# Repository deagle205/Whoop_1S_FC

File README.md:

# Phil: 1S whoop flight controller (KiCad 10)

Three stacked 19x19 / 16x16 boards on a 12.8 mm M1.4 screw square:

- `Whoop_1S_FC.*`: flight controller (STM32G473 WLCSP-81, ICM-42688-P, SPL06, ELRS SX1281 + ESP8285, TPS63802)
- `Phil_ESC/`: 4-in-1 Bluejay ESC (4x EFM8BB51, 12x SiA517DJ)
- `Phil_VTX/`: 5.8 GHz VTX (RTC6705 + SE5004L), AT7456E OSD, blackbox flash, 5 V boost

Shared libraries: `WhoopFC.kicad_sym`, `WhoopFC.pretty/`, `WhoopFC.3dshapes/`.
Note: 3D model paths in the footprints are absolute (C:/Users/Survi/...), so other machines won't show them without editing.

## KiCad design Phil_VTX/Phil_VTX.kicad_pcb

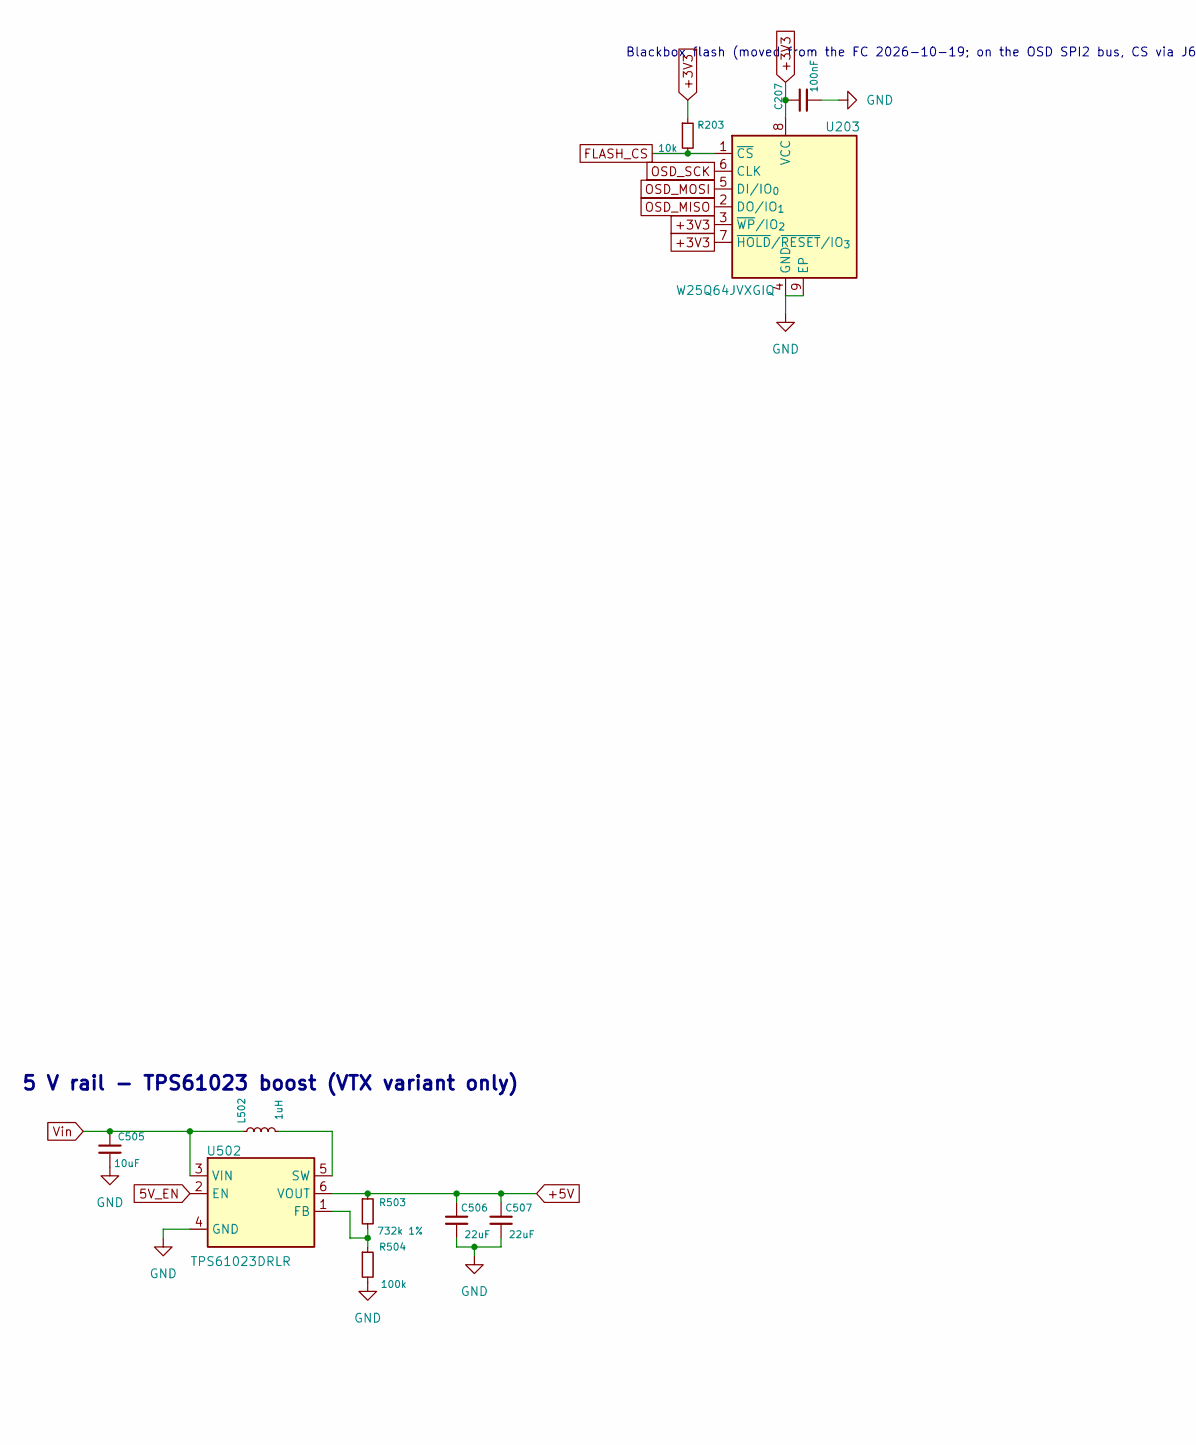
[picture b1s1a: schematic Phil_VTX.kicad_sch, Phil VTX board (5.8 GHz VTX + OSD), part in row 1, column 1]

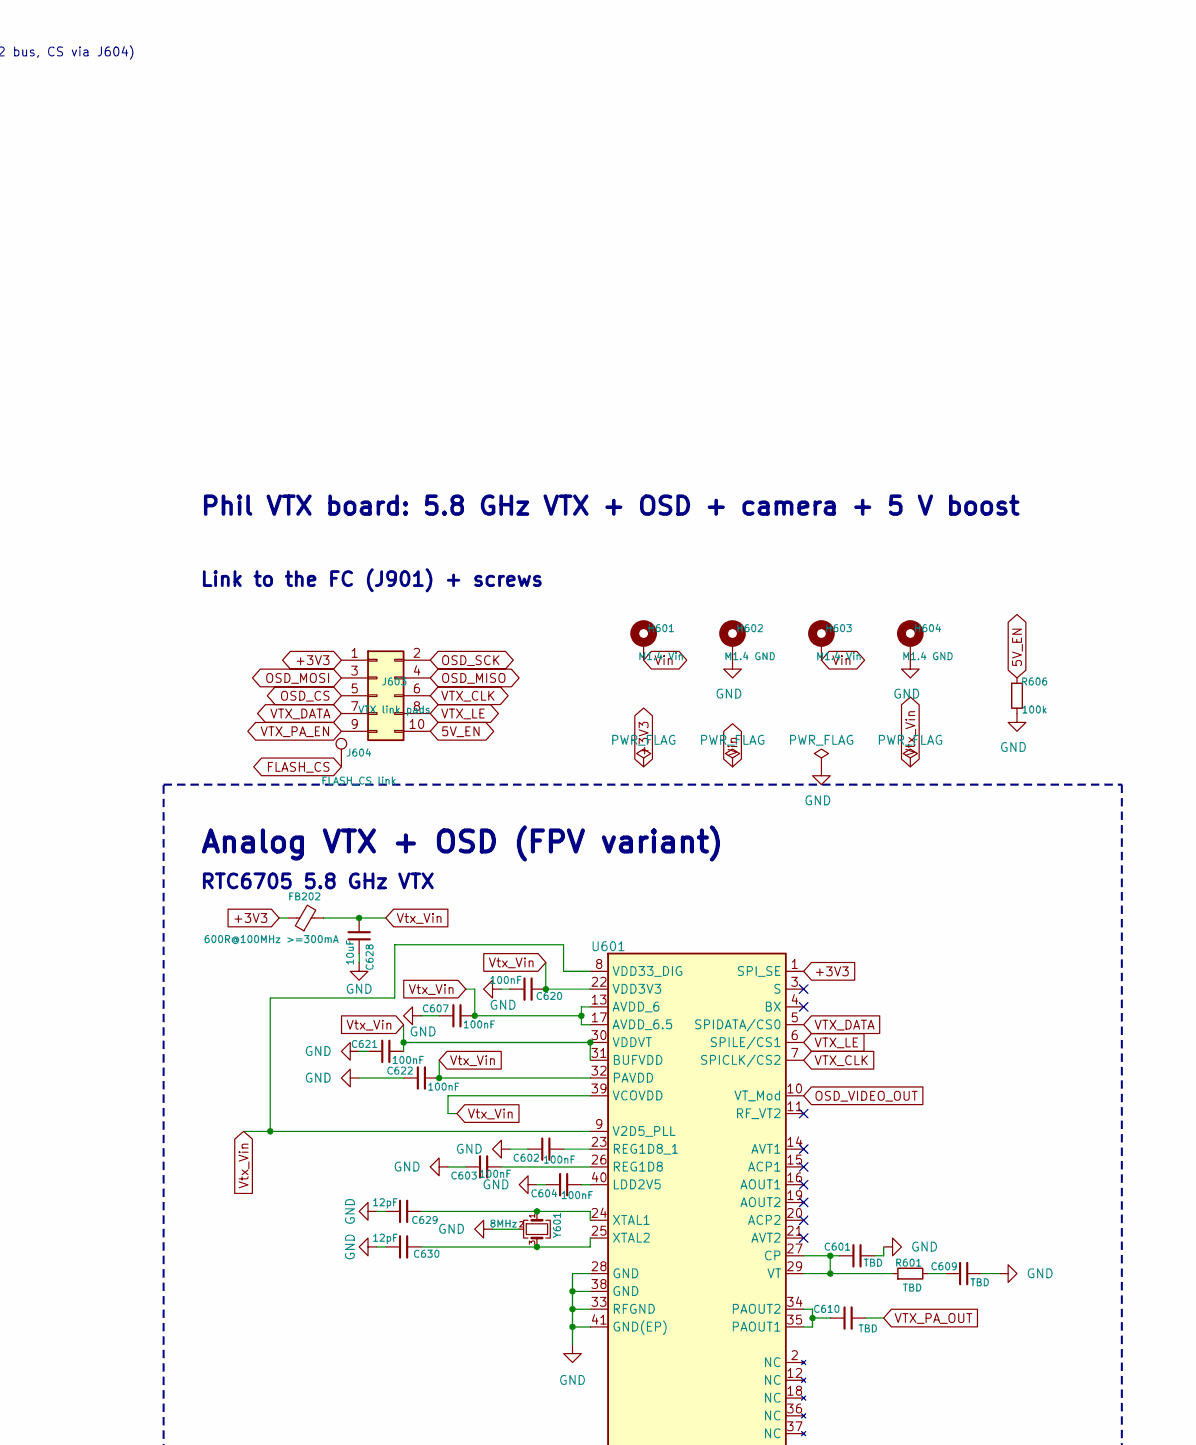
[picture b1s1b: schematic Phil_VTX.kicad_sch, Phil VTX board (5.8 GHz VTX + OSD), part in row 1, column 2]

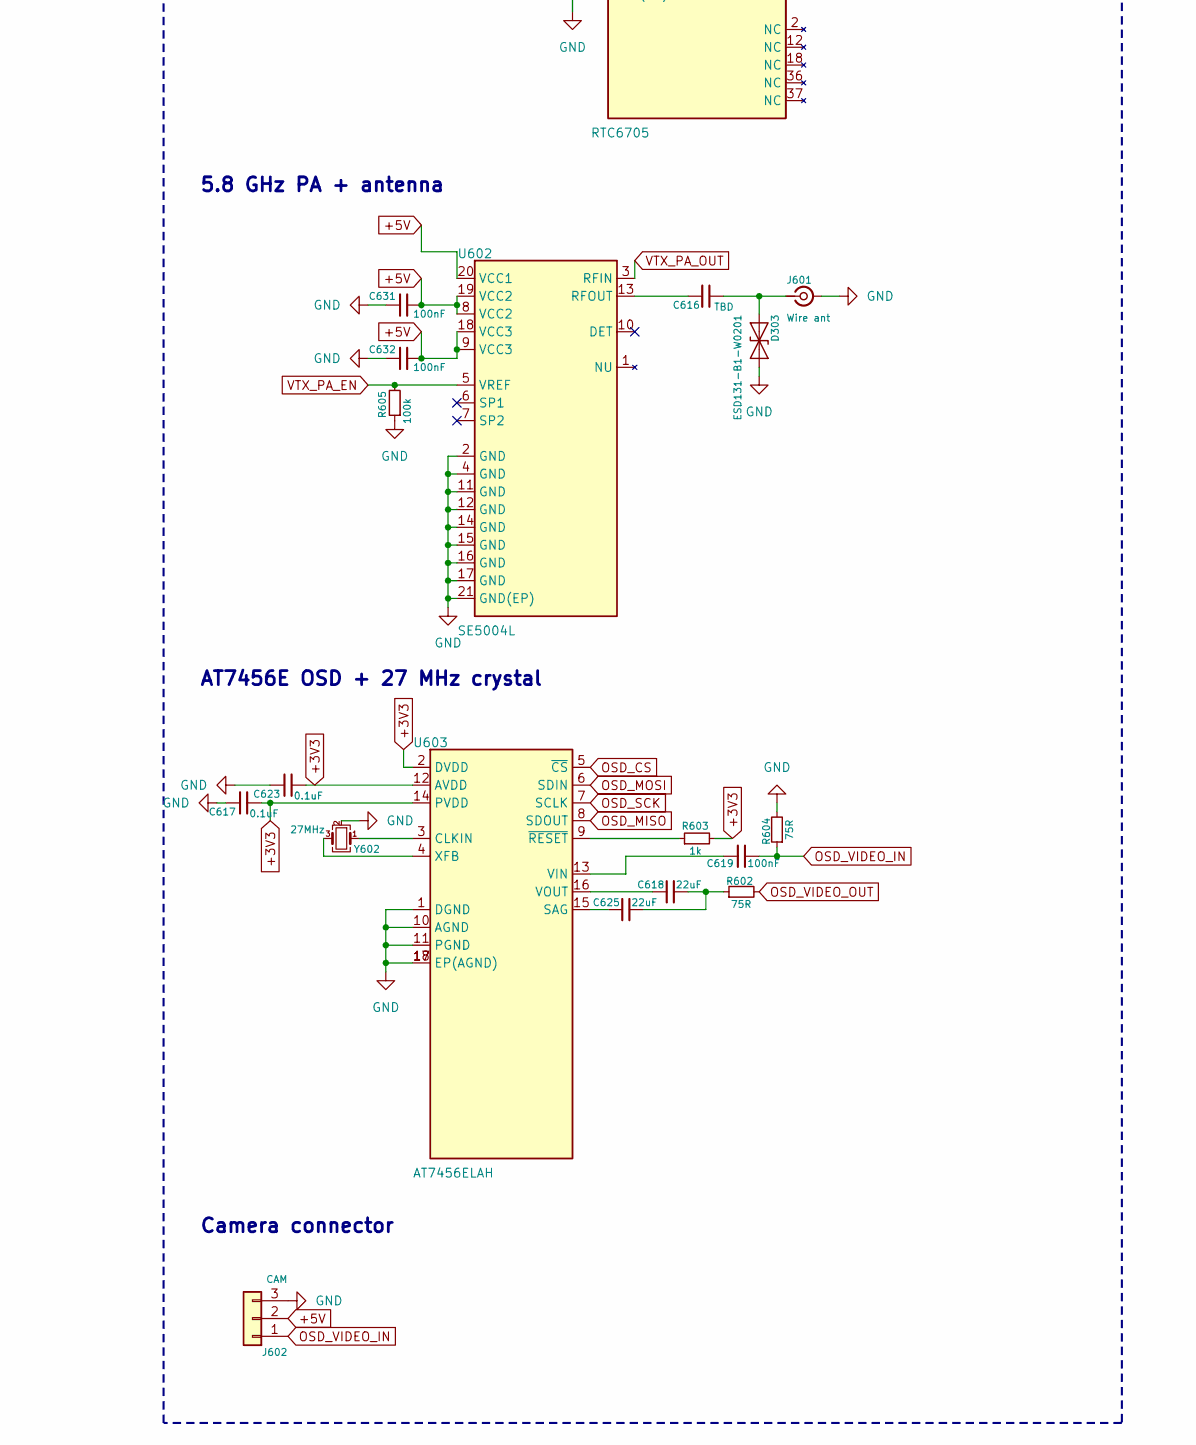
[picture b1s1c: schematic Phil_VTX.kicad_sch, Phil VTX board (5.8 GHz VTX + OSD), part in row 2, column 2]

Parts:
C207, C602, C603, C604, C607, C619, C620, C621, C622, C631, C632: 100nF; C_0201_0603Metric; MPN CL03A104KQ3NNNC; LCSC C160831
C505, C628: 10uF; C_0603_1608Metric; MPN CL10A106KP8NNNC; LCSC C19702
C506, C507, C618, C625: 22uF; C_0603_1608Metric; MPN CL10A226MP8NUNE; LCSC C86295
C601, C609, C610, C616: TBD; C_0201_0603Metric
C617, C623: 0.1uF; C_0201_0603Metric; MPN CL03A104KQ3NNNC; LCSC C160831
C629, C630: 12pF; C_0201_0603Metric; MPN GRM0335C1H120JA01D; LCSC C85890
D303: ESD131-B1-W0201; Infineon_SG-WLL-2-3_0.58x0.28_P0.36mm; MPN ESD131-B1-W0201
FB202: 600R@100MHz >=300mA; L_0603_1608Metric
H601, H603: M1.4 Vin; MountingHole_1.6mm_M1.4_Pad_2.6mm
H602, H604: M1.4 GND; MountingHole_1.6mm_M1.4_Pad_2.6mm
J601: Wire ant; Antenna_Wire_Hole_D0.6mm
J602: CAM; Pads_1x03_P2.0mm_1.5x2.0mm; MPN SM03B-SRSS-TB
J603: VTX link pads; Pads_2x05_P1.8mm_1.5x2.0mm_Mirrored
J604: FLASH_CS link; TP_Wire_1.5x2.0mm
L502: 1uH; L_Murata_DFE201610P
R203: 10k; R_0201_0603Metric; MPN RC0201FR-0710KL; LCSC C106225
R503: 732k 1%; R_0201_0603Metric; MPN AA0201FR-07732KL; LCSC C2106378
R504, R605, R606: 100k; R_0201_0603Metric; MPN 0201WMF1003TEE; LCSC C270364
R601: TBD; R_0201_0603Metric
R602, R604: 75R; R_0201_0603Metric; MPN 0201WMF750JTCE; LCSC C270688
R603: 1k; R_0201_0603Metric; MPN 0201WMF1001TEE; LCSC C270365
U203: W25Q64JVXGIQ; Winbond_XSON-8-1EP_4x4mm_P0.8mm_EP2.3x3mm; MPN W25Q64JVXGIQ
U502: TPS61023DRLR; SOT-563; MPN TPS61023DRLR
U601: RTC6705; QFN-40-1EP_6x6mm_P0.5mm_EP4.6x4.6mm; MPN RTC6705
U602: SE5004L; QFN-20-1EP_4x4mm_P0.5mm_EP2.5x2.5mm; MPN SE5004L
U603: AT7456ELAH; AT7456E_LGA-16_4x6.8mm_P0.65mm; MPN AT7456E
Y601: 8MHz; Crystal_SMD_2016-4Pin_2.0x1.6mm
Y602: 27MHz; Crystal_SMD_WE_IQXC-26-4Pin_1.6x1.2mm

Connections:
5V_EN: J603.10, R606.1, U502.2 (EN)
+3V3: C207.1, C617.2, C623.2, FB202.1, J603.1, R203.1, R603.2, U203.3 (~WP/IO_{2}), U203.7 (~HOLD/~RESET/IO_{3}), U203.8 (VCC), U601.1 (SPI_SE), U603.2 (DVDD), U603.12 (AVDD), U603.14 (PVDD)
+5V: C506.1, C507.1, C631.2, C632.2, J602.2, R503.1, U502.6 (VOUT), U602.8 (VCC2), U602.9 (VCC3), U602.18 (VCC3), U602.19 (VCC2), U602.20 (VCC1)
GND: C207.2, C505.2, C506.2, C507.2, C601.2, C602.1, C603.1, C604.1, C607.1, C609.2, C617.1, C620.2, C621.1, C622.1, C623.1, C628.2, C629.2, C630.2, C631.1, C632.1, D303.2 (A2), H602.1, H604.1, J601.2 (Ext), J602.3, R504.2, R604.2, R605.1, R606.2, U203.4 (GND), U203.9 (EP), U502.4 (GND), U601.28 (GND), U601.33 (RFGND), U601.38 (GND), U601.41 (GND(EP)), U602.2 (GND), U602.4 (GND), U602.11 (GND), U602.12 (GND), U602.14 (GND), U602.15 (GND), U602.16 (GND), U602.17 (GND), U602.21 (GND(EP)), U603.1 (DGND), U603.10 (AGND), U603.11 (PGND), U603.17 (EP(AGND)), U603.18 (EP(AGND)), Y601.2 (G), Y601.4 (G), Y602.2 (G), Y602.4 (G)
unnamed: C609.1, R601.2
unnamed: C618.2, C625.2, R602.1
unnamed: C616.2, D303.1 (A1), J601.1 (In)
unnamed: J604.1, R203.2, U203.1 (~CS)
unnamed: R503.2, R504.1, U502.1 (FB)
unnamed: L502.2, U502.5 (SW)
unnamed: C601.1, R601.1, U601.27 (CP), U601.29 (VT)
unnamed: C604.2, U601.40 (LDD2V5)
unnamed: C610.1, U601.34 (PAOUT2), U601.35 (PAOUT1)
unnamed: C603.2, U601.26 (REG1D8)
unnamed: C602.2, U601.23 (REG1D8_1)
unnamed: C629.1, U601.24 (XTAL1), Y601.1
unnamed: C630.1, U601.25 (XTAL2), Y601.3
unnamed: C616.1, U602.13 (RFOUT)
unnamed: U603.3 (CLKIN), Y602.1
unnamed: C625.1, U603.15 (SAG)
unnamed: C619.1, U603.13 (VIN)
unnamed: C618.1, U603.16 (VOUT)
unnamed: U603.4 (XFB), Y602.3
unnamed: R603.1, U603.9 (~RESET)
OSD_CS: J603.5, U603.5 (~CS)
OSD_MISO: J603.4, U203.2 (DO/IO_{1}), U603.8 (SDOUT)
OSD_MOSI: J603.3, U203.5 (DI/IO_{0}), U603.6 (SDIN)
OSD_SCK: J603.2, U203.6 (CLK), U603.7 (SCLK)
OSD_VIDEO_IN: C619.2, J602.1, R604.1
OSD_VIDEO_OUT: R602.2, U601.10 (VT_Mod)
VTX_CLK: J603.6, U601.7 (SPICLK/CS2)
VTX_DATA: J603.7, U601.5 (SPIDATA/CS0)
VTX_LE: J603.8, U601.6 (SPILE/CS1)
VTX_PA_EN: J603.9, R605.2, U602.5 (VREF)
VTX_PA_OUT: C610.2, U602.3 (RFIN)
Vin: C505.1, H601.1, H603.1, L502.1, U502.3 (VIN)
Vtx_Vin: C607.2, C620.1, C621.2, C622.2, C628.1, FB202.2, U601.8 (VDD33_DIG), U601.9 (V2D5_PLL), U601.13 (AVDD_6), U601.17 (AVDD_6.5), U601.22 (VDD3V3), U601.30 (VDDVT), U601.31 (BUFVDD), U601.32 (PAVDD), U601.39 (VCOVDD)

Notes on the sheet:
5 V rail - TPS61023 boost (VTX variant only)
5.8 GHz PA + antenna
RTC6705 5.8 GHz VTX
Blackbox flash (moved from the FC 2026-10-19; on the OSD SPI2 bus, CS via J604)
Phil VTX board: 5.8 GHz VTX + OSD + camera + 5 V boost
Link to the FC (J901) + screws
AT7456E OSD + 27 MHz crystal
Camera connector
Analog VTX + OSD (FPV variant)

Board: 6 copper layers, 48 parts (0 on the bottom side), 36 nets, no tracks yet.

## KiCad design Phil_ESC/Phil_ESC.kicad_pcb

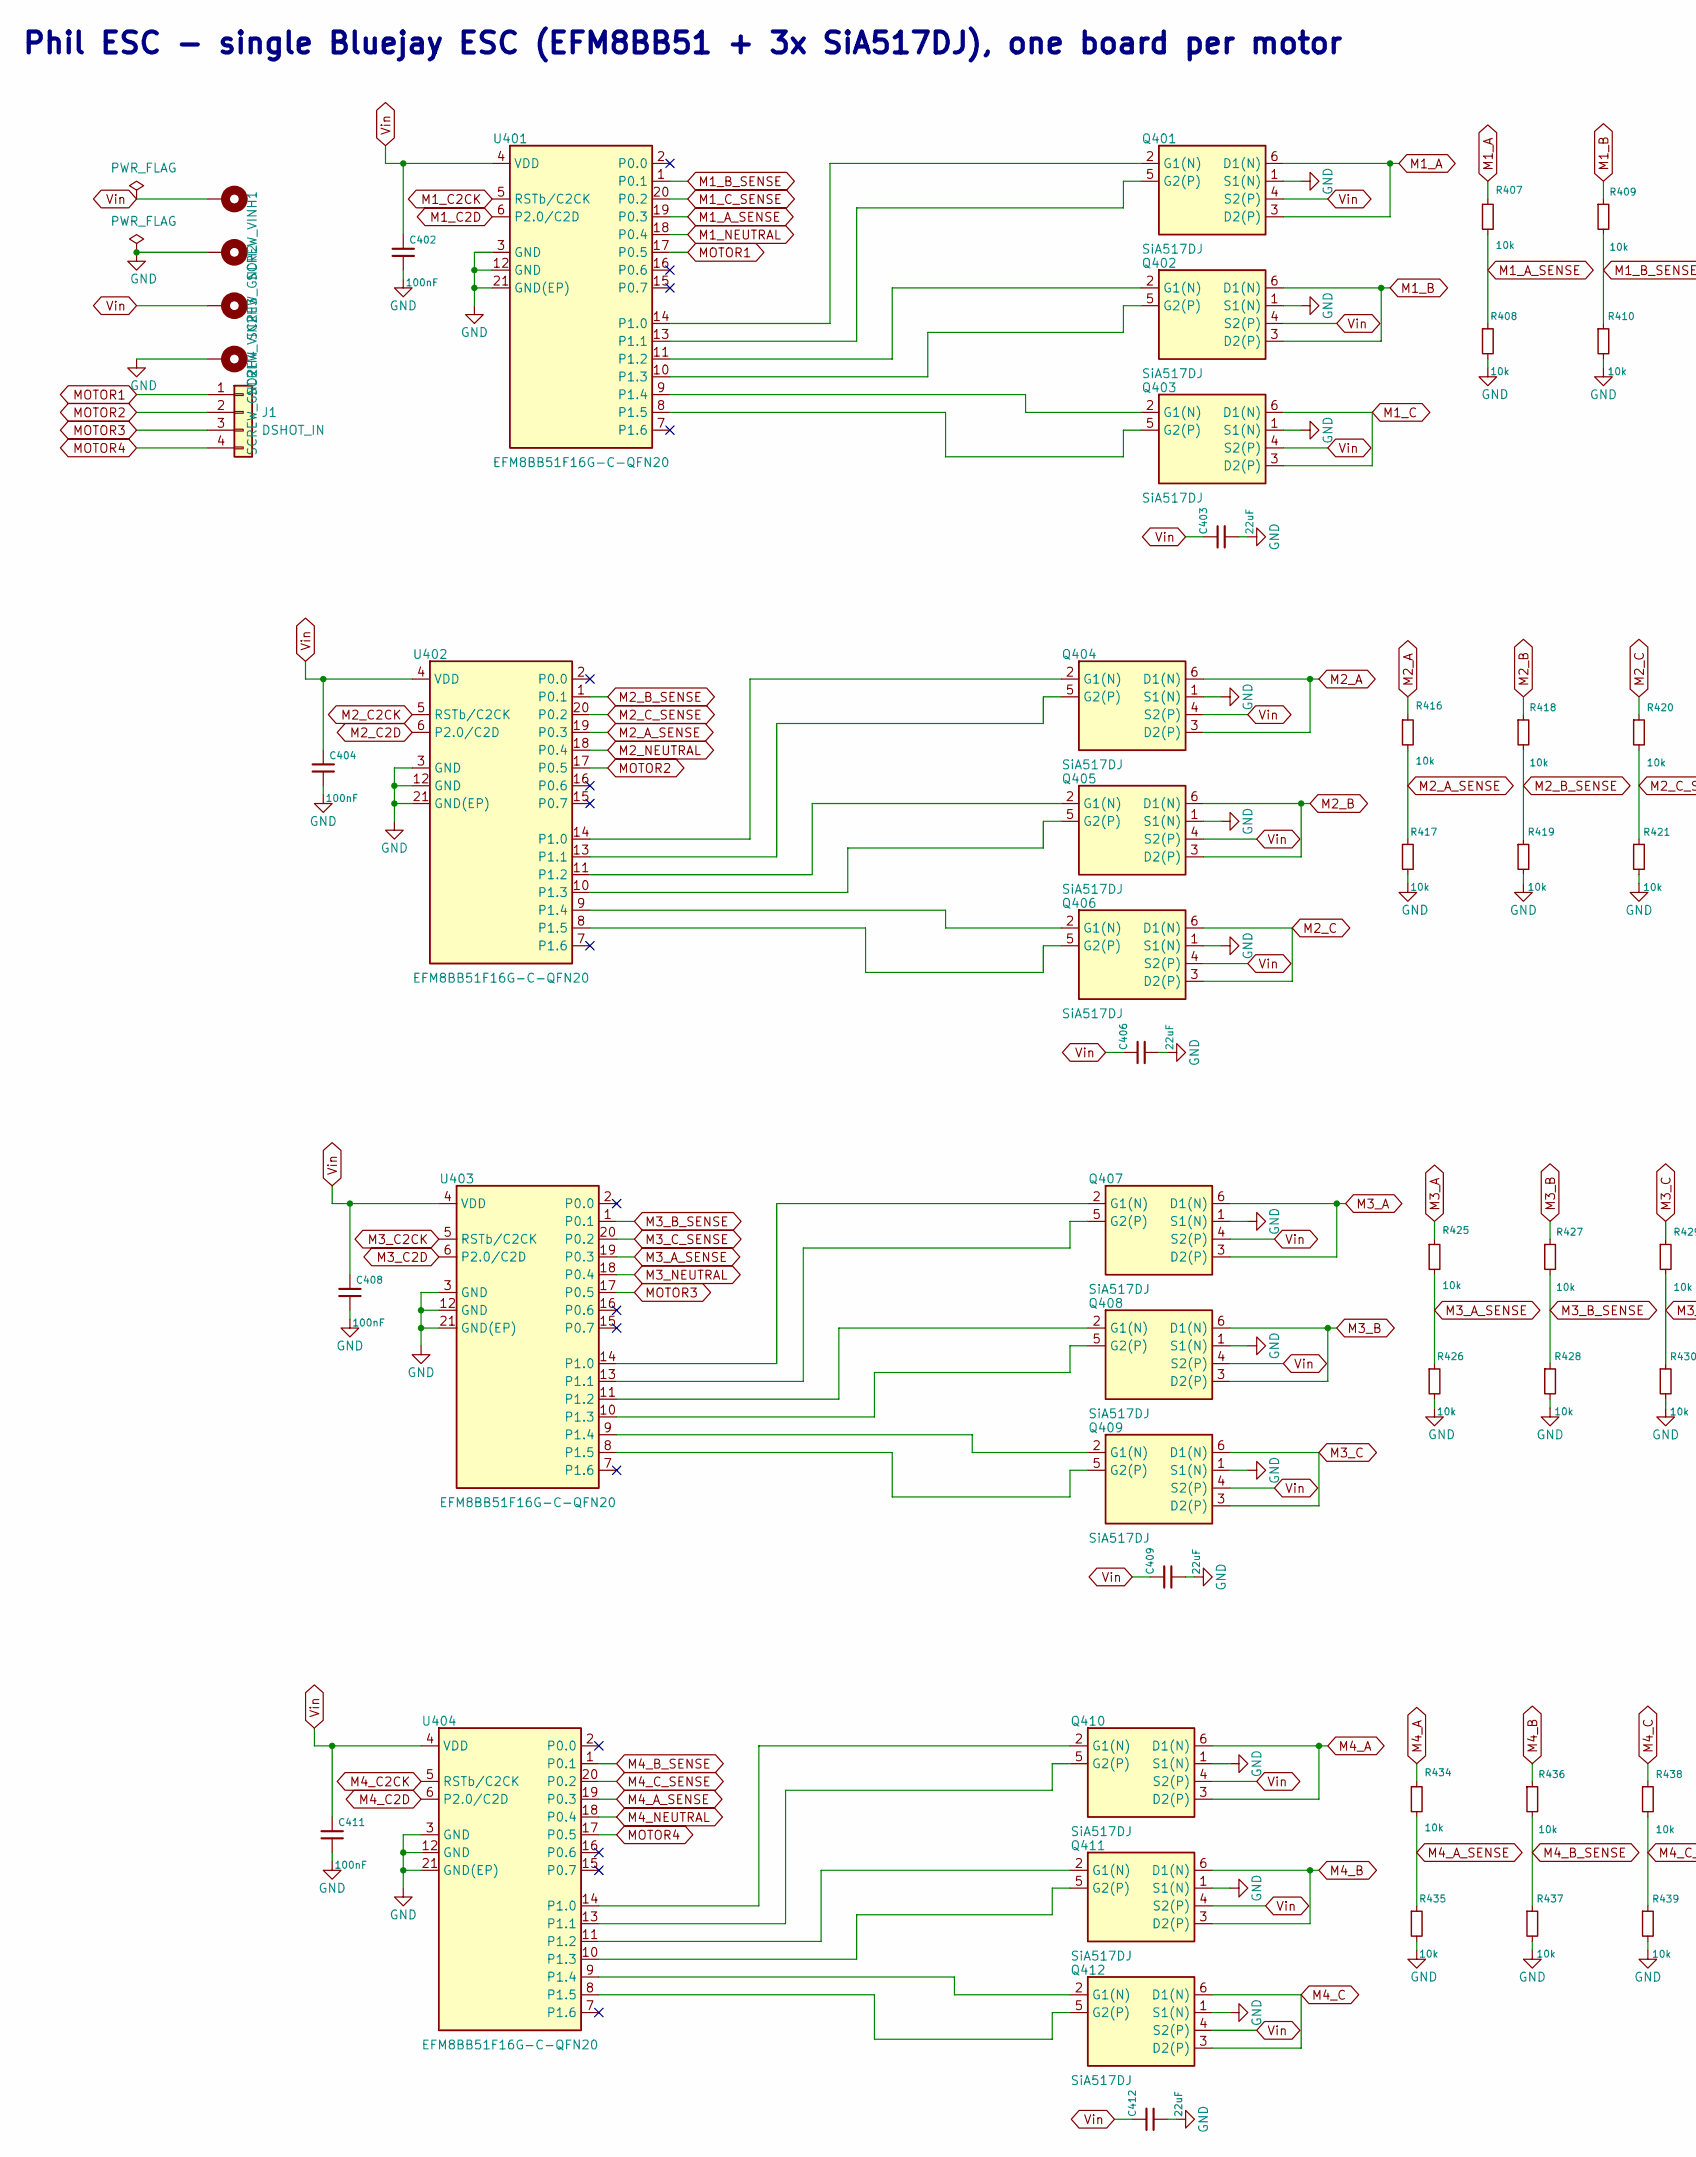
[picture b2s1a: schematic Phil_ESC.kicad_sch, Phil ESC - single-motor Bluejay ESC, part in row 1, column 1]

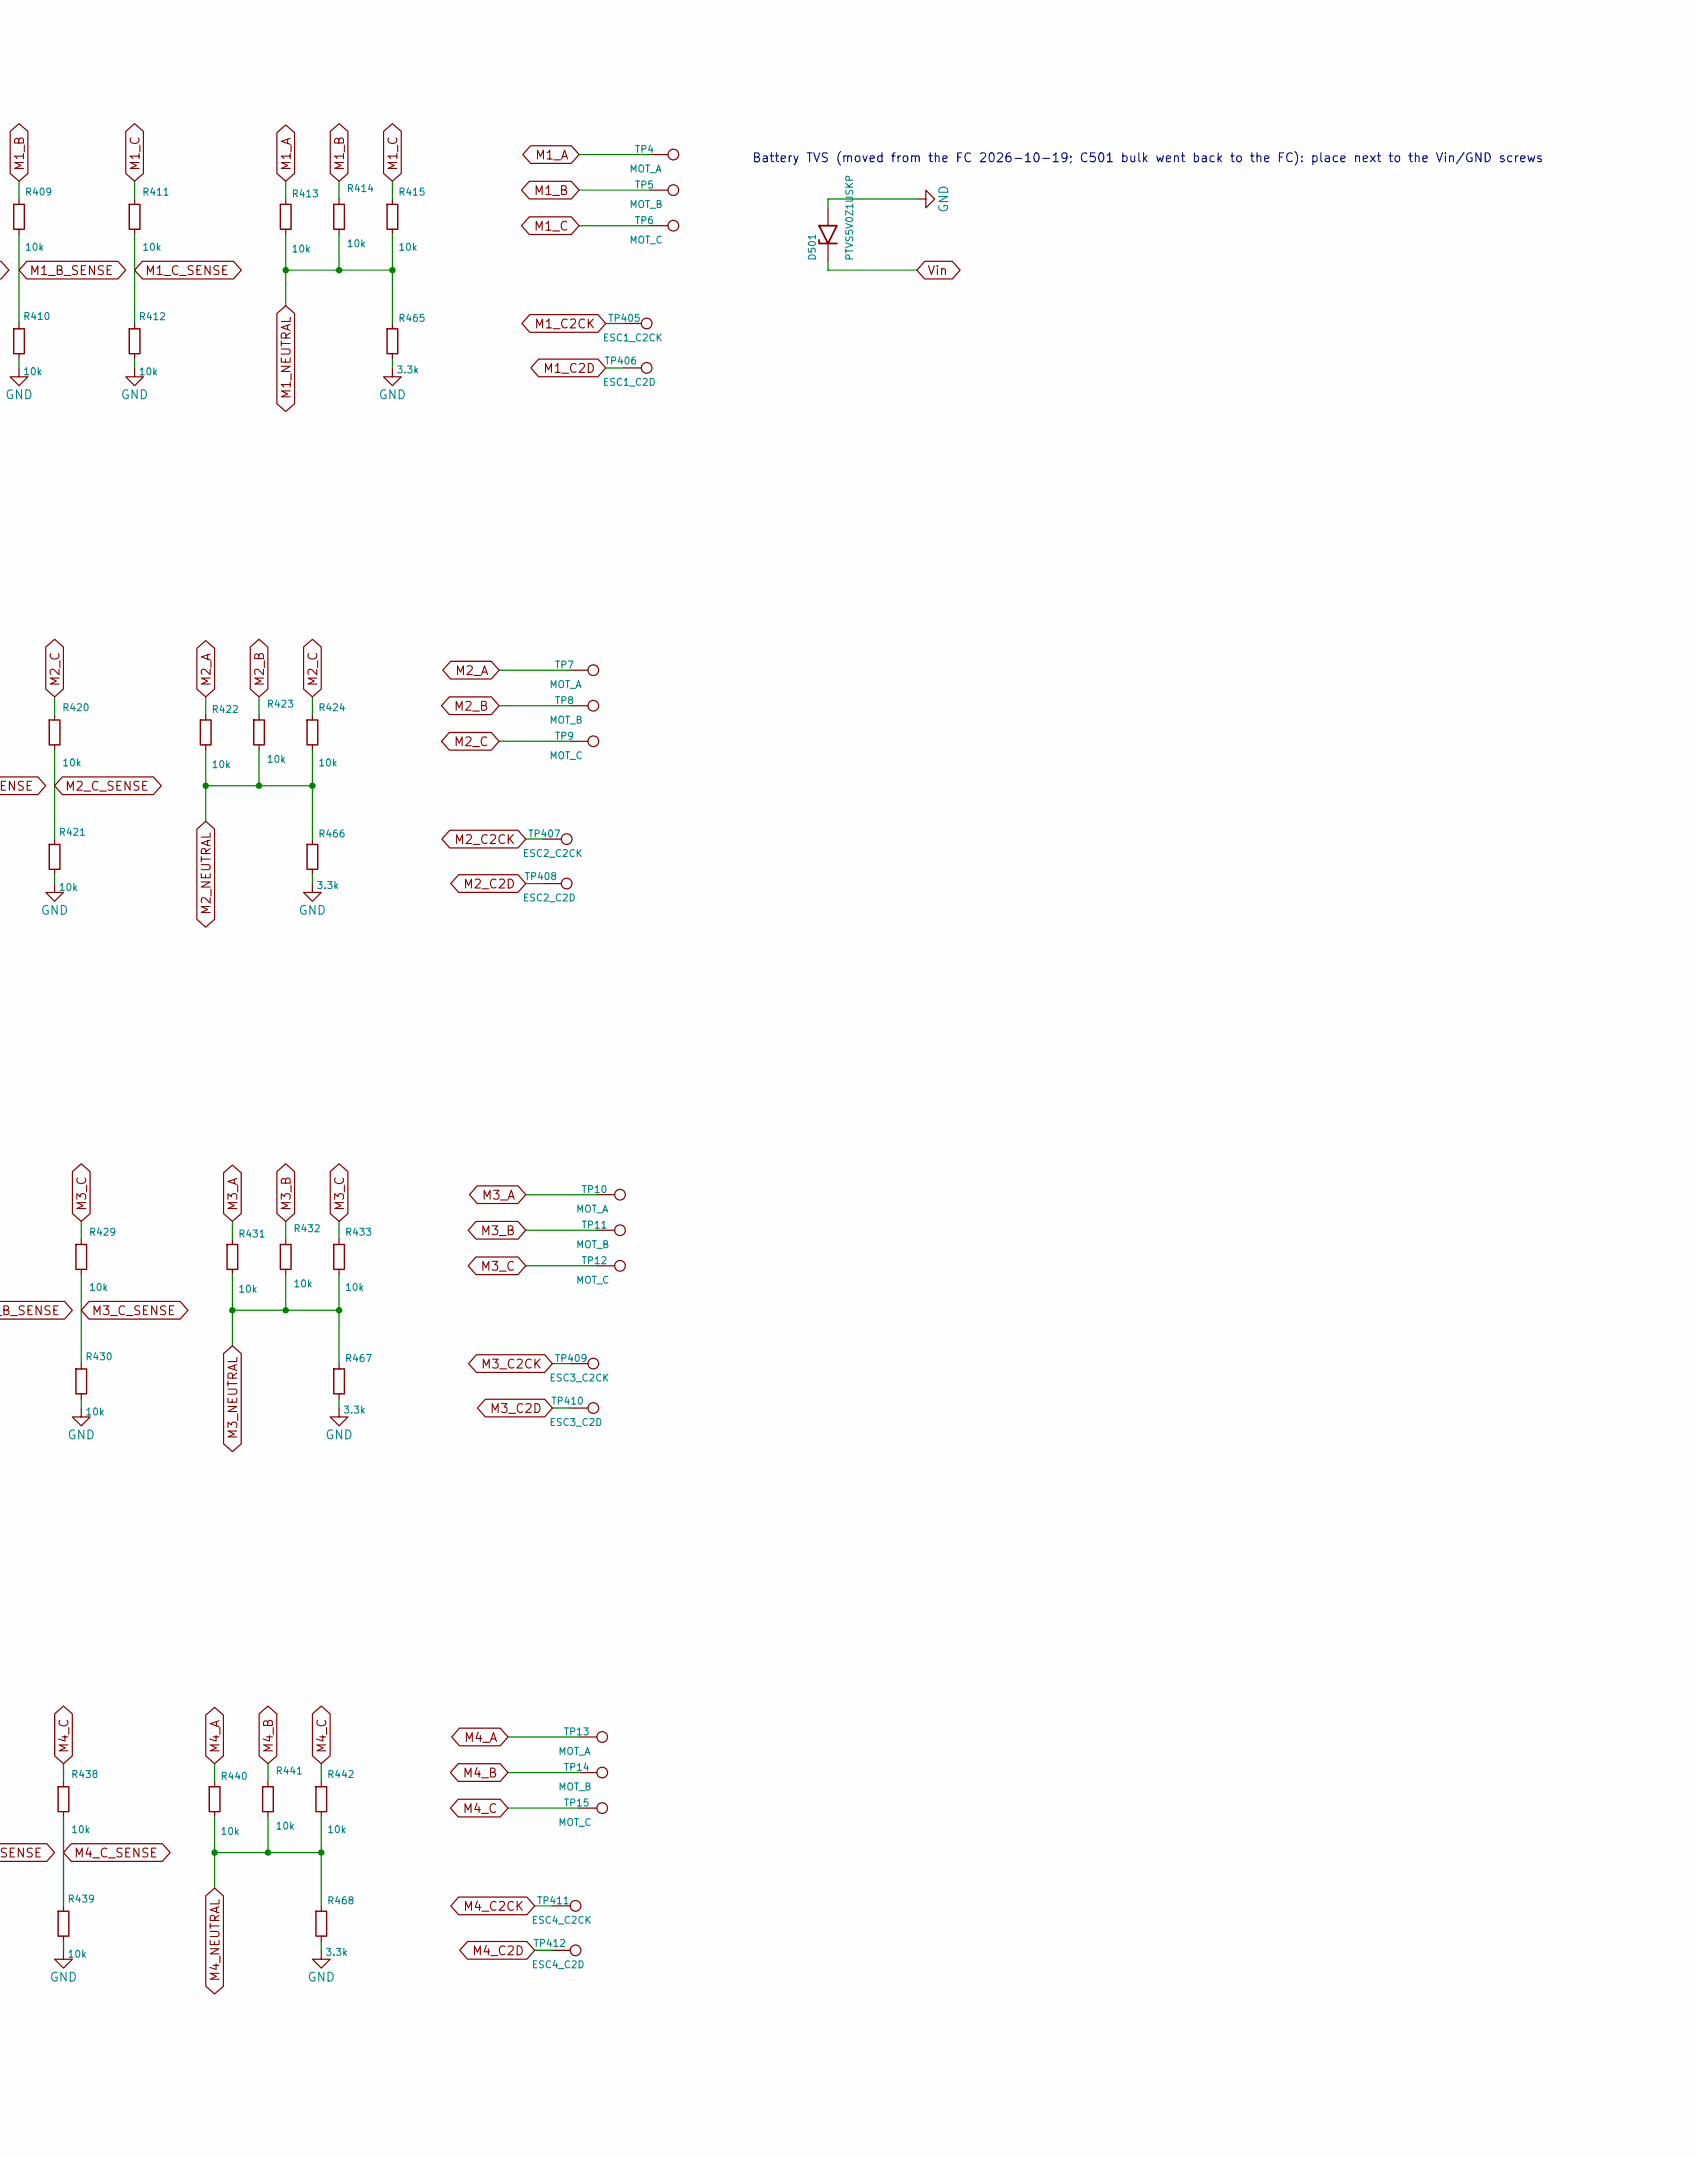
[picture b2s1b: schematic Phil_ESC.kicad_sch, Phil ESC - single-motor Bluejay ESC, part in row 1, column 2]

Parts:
C402, C404, C408, C411: 100nF; C_0201_0603Metric; MPN CL03A104KQ3NNNC; LCSC C160831
C403, C406, C409, C412: 22uF; C_0603_1608Metric; MPN CL10A226MP8NUNE; LCSC C86295
D501: PTVS5V0Z1USKP; Nexperia_DSN1608-2_1.6x0.8mm; MPN PTVS5V0Z1USKP
H1: SCREW_VIN; MountingHole_1.6mm_M1.4_Pad_2.6mm
H2: SCREW_GND; MountingHole_1.6mm_M1.4_Pad_2.6mm
H3: SCREW_VIN2; MountingHole_1.6mm_M1.4_Pad_2.6mm
H4: SCREW_GND2; MountingHole_1.6mm_M1.4_Pad_2.6mm
J1: DSHOT_IN; PinHeader_1x04_P1.27mm_Vertical
Q401, Q402, Q403, Q404, Q405, Q406, Q407, Q408, Q409, Q410, Q411, Q412: SiA517DJ; Vishay_PowerPAK_SC70-6L_Dual; MPN SIA517DJ-T1-GE3
R407, R408, R409, R410, R411, R412, R413, R414, R415, R416, R417, R418, R419, R420, R421, R422, R423, R424, R425, R426, R427, R428, R429, R430, R431, R432, R433, R434, R435, R436, R437, R438, R439, R440, R441, R442: 10k; R_0201_0603Metric; MPN RC0201FR-0710KL; LCSC C106225
R465, R466, R467, R468: 3.3k; R_0201_0603Metric; MPN RC0201FR-073K3L; LCSC C274874
TP4, TP7, TP10, TP13: MOT_A; TP_Motor_1.5x1.5mm
TP5, TP8, TP11, TP14: MOT_B; TP_Motor_1.5x1.5mm
TP6, TP9, TP12, TP15: MOT_C; TP_Motor_1.5x1.5mm
TP405: ESC1_C2CK; TP_Probe_D0.6mm
TP406: ESC1_C2D; TP_Probe_D0.6mm
TP407: ESC2_C2CK; TP_Probe_D0.6mm
TP408: ESC2_C2D; TP_Probe_D0.6mm
TP409: ESC3_C2CK; TP_Probe_D0.6mm
TP410: ESC3_C2D; TP_Probe_D0.6mm
TP411: ESC4_C2CK; TP_Probe_D0.6mm
TP412: ESC4_C2D; TP_Probe_D0.6mm
U401, U402, U403, U404: EFM8BB51F16G-C-QFN20; SiliconLabs_QFN-20-1EP_3x3mm_P0.5mm_EP1.8x1.8mm; MPN EFM8BB51F16G-C-QFN20

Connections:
GND: C402.2, C403.2, C404.2, C406.2, C408.2, C409.2, C411.2, C412.2, D501.2 (A2), H2.1 (1_1), H4.1 (1_1), Q401.1 (S1(N)), Q402.1 (S1(N)), Q403.1 (S1(N)), Q404.1 (S1(N)), Q405.1 (S1(N)), Q406.1 (S1(N)), Q407.1 (S1(N)), Q408.1 (S1(N)), Q409.1 (S1(N)), Q410.1 (S1(N)), Q411.1 (S1(N)), Q412.1 (S1(N)), R408.2, R410.2, R412.2, R417.2, R419.2, R421.2, R426.2, R428.2, R430.2, R435.2, R437.2, R439.2, R465.2, R466.2, R467.2, R468.2, U401.3 (GND), U401.12 (GND), U401.21 (GND(EP)), U402.3 (GND), U402.12 (GND), U402.21 (GND(EP)), U403.3 (GND), U403.12 (GND), U403.21 (GND(EP)), U404.3 (GND), U404.12 (GND), U404.21 (GND(EP))
M1_A: Q401.3 (D2(P)), Q401.6 (D1(N)), R407.1, R413.1, TP4.1 (1_1)
M1_A_SENSE: R407.2, R408.1, U401.19 (P0.3)
M1_B: Q402.3 (D2(P)), Q402.6 (D1(N)), R409.1, R414.1, TP5.1 (1_1)
M1_B_SENSE: R409.2, R410.1, U401.1 (P0.1)
M1_C: Q403.3 (D2(P)), Q403.6 (D1(N)), R411.1, R415.1, TP6.1 (1_1)
M1_C2CK: TP405.1 (1_1), U401.5 (RSTb/C2CK)
M1_C2D: TP406.1 (1_1), U401.6 (P2.0/C2D)
M1_C_SENSE: R411.2, R412.1, U401.20 (P0.2)
M1_NEUTRAL: R413.2, R414.2, R415.2, R465.1, U401.18 (P0.4)
M2_A: Q404.3 (D2(P)), Q404.6 (D1(N)), R416.1, R422.1, TP7.1 (1_1)
M2_A_SENSE: R416.2, R417.1, U402.19 (P0.3)
M2_B: Q405.3 (D2(P)), Q405.6 (D1(N)), R418.1, R423.1, TP8.1 (1_1)
M2_B_SENSE: R418.2, R419.1, U402.1 (P0.1)
M2_C: Q406.3 (D2(P)), Q406.6 (D1(N)), R420.1, R424.1, TP9.1 (1_1)
M2_C2CK: TP407.1 (1_1), U402.5 (RSTb/C2CK)
M2_C2D: TP408.1 (1_1), U402.6 (P2.0/C2D)
M2_C_SENSE: R420.2, R421.1, U402.20 (P0.2)
M2_NEUTRAL: R422.2, R423.2, R424.2, R466.1, U402.18 (P0.4)
M3_A: Q407.3 (D2(P)), Q407.6 (D1(N)), R425.1, R431.1, TP10.1 (1_1)
M3_A_SENSE: R425.2, R426.1, U403.19 (P0.3)
M3_B: Q408.3 (D2(P)), Q408.6 (D1(N)), R427.1, R432.1, TP11.1 (1_1)
M3_B_SENSE: R427.2, R428.1, U403.1 (P0.1)
M3_C: Q409.3 (D2(P)), Q409.6 (D1(N)), R429.1, R433.1, TP12.1 (1_1)
M3_C2CK: TP409.1 (1_1), U403.5 (RSTb/C2CK)
M3_C2D: TP410.1 (1_1), U403.6 (P2.0/C2D)
M3_C_SENSE: R429.2, R430.1, U403.20 (P0.2)
M3_NEUTRAL: R431.2, R432.2, R433.2, R467.1, U403.18 (P0.4)
M4_A: Q410.3 (D2(P)), Q410.6 (D1(N)), R434.1, R440.1, TP13.1 (1_1)
M4_A_SENSE: R434.2, R435.1, U404.19 (P0.3)
M4_B: Q411.3 (D2(P)), Q411.6 (D1(N)), R436.1, R441.1, TP14.1 (1_1)
M4_B_SENSE: R436.2, R437.1, U404.1 (P0.1)
M4_C: Q412.3 (D2(P)), Q412.6 (D1(N)), R438.1, R442.1, TP15.1 (1_1)
M4_C2CK: TP411.1 (1_1), U404.5 (RSTb/C2CK)
M4_C2D: TP412.1 (1_1), U404.6 (P2.0/C2D)
M4_C_SENSE: R438.2, R439.1, U404.20 (P0.2)
M4_NEUTRAL: R440.2, R441.2, R442.2, R468.1, U404.18 (P0.4)
MOTOR1: J1.1, U401.17 (P0.5)
MOTOR2: J1.2, U402.17 (P0.5)
MOTOR3: J1.3, U403.17 (P0.5)
MOTOR4: J1.4, U404.17 (P0.5)
unnamed: Q401.2 (G1(N)), U401.14 (P1.0)
unnamed: Q401.5 (G2(P)), U401.13 (P1.1)
unnamed: Q402.2 (G1(N)), U401.11 (P1.2)
unnamed: Q402.5 (G2(P)), U401.10 (P1.3)
unnamed: Q403.2 (G1(N)), U401.9 (P1.4)
unnamed: Q403.5 (G2(P)), U401.8 (P1.5)
unnamed: Q404.2 (G1(N)), U402.14 (P1.0)
unnamed: Q404.5 (G2(P)), U402.13 (P1.1)
unnamed: Q405.2 (G1(N)), U402.11 (P1.2)
unnamed: Q405.5 (G2(P)), U402.10 (P1.3)
unnamed: Q406.2 (G1(N)), U402.9 (P1.4)
unnamed: Q406.5 (G2(P)), U402.8 (P1.5)
unnamed: Q407.2 (G1(N)), U403.14 (P1.0)
unnamed: Q407.5 (G2(P)), U403.13 (P1.1)
unnamed: Q408.2 (G1(N)), U403.11 (P1.2)
unnamed: Q408.5 (G2(P)), U403.10 (P1.3)
unnamed: Q409.2 (G1(N)), U403.9 (P1.4)
unnamed: Q409.5 (G2(P)), U403.8 (P1.5)
unnamed: Q410.2 (G1(N)), U404.14 (P1.0)
unnamed: Q410.5 (G2(P)), U404.13 (P1.1)
unnamed: Q411.2 (G1(N)), U404.11 (P1.2)
unnamed: Q411.5 (G2(P)), U404.10 (P1.3)
unnamed: Q412.2 (G1(N)), U404.9 (P1.4)
unnamed: Q412.5 (G2(P)), U404.8 (P1.5)
Vin: C402.1, C403.1, C404.1, C406.1, C408.1, C409.1, C411.1, C412.1, D501.1 (A1), H1.1 (1_1), H3.1 (1_1), Q401.4 (S2(P)), Q402.4 (S2(P)), Q403.4 (S2(P)), Q404.4 (S2(P)), Q405.4 (S2(P)), Q406.4 (S2(P)), Q407.4 (S2(P)), Q408.4 (S2(P)), Q409.4 (S2(P)), Q410.4 (S2(P)), Q411.4 (S2(P)), Q412.4 (S2(P)), U401.4 (VDD), U402.4 (VDD), U403.4 (VDD), U404.4 (VDD)

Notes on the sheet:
Phil ESC - single Bluejay ESC (EFM8BB51 + 3x SiA517DJ), one board per motor
Battery TVS (moved from the FC 2026-10-19; C501 bulk went back to the FC): place next to the Vin/GND screws

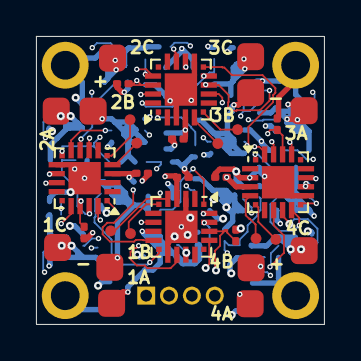
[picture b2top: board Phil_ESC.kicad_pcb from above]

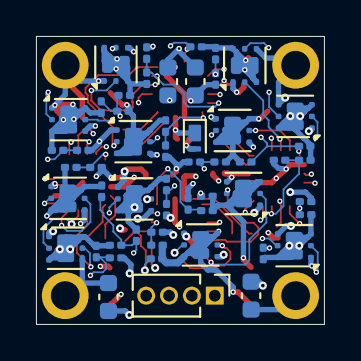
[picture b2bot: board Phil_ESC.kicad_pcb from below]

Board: 6 copper layers, 16.0 x 16.0 mm, 90 parts (54 on the bottom side), 66 nets.
